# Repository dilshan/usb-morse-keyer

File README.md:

# USB Morse Keyer

USB Morse Keyer is microcontroller based keyer with following features:

- USB / straight key / iambic key inputs.
- Support for both *standalone* and *USB* operating modes.
- 64-character USB typeahead buffer and 6-character Morse key typeahead buffer.
- Support 5, 10, 15 WPM.
- 6-page message memory.
- 1W Audio output.
- Audio and PTT output interfaces.
- 32 character display

To reduce the dimension of the PCB this unit is designed with combining both through-hole and surface mount components. To facilitate future upgrades and modifications, the *PIC16F886* MCU sticks with the standard 28-pin DIP package.

The USB interface of this unit is designed to work with most of the operating systems. It emulates a virtual serial terminal to transfer keystrokes to the keyer. In most of the operating systems, this interface works without installing any additional device drivers. To submit keystrokes user can use any serial terminal software such as [PuTTY](https://www.putty.org), *Hyper Terminal*, [Minicom](https://salsa.debian.org/minicom-team/minicom), etc. 

This keyer is designed to work with 7V to 16V DC input voltage. The most recommended working voltage is 9V.

[All the details related to this project are available at project documentation.](https://github.com/dilshan/usb-morse-keyer/wiki)

## Licenses

This is a [certified](https://certification.oshwa.org/lk000004.html) open hardware project and all it's design files, firmware source codes, [documentation](https://github.com/dilshan/usb-morse-keyer/wiki), and other resource files are available at the project source repository. All the content of this project are distributed under the terms of the following license:

- Hardware License: [CC BY 4.0](https://creativecommons.org/licenses/by/4.0/)
- Software License: [MIT](https://github.com/dilshan/usb-morse-keyer/blob/master/LICENSE)
- Documentation License: [CC BY 4.0](https://creativecommons.org/licenses/by/4.0/)

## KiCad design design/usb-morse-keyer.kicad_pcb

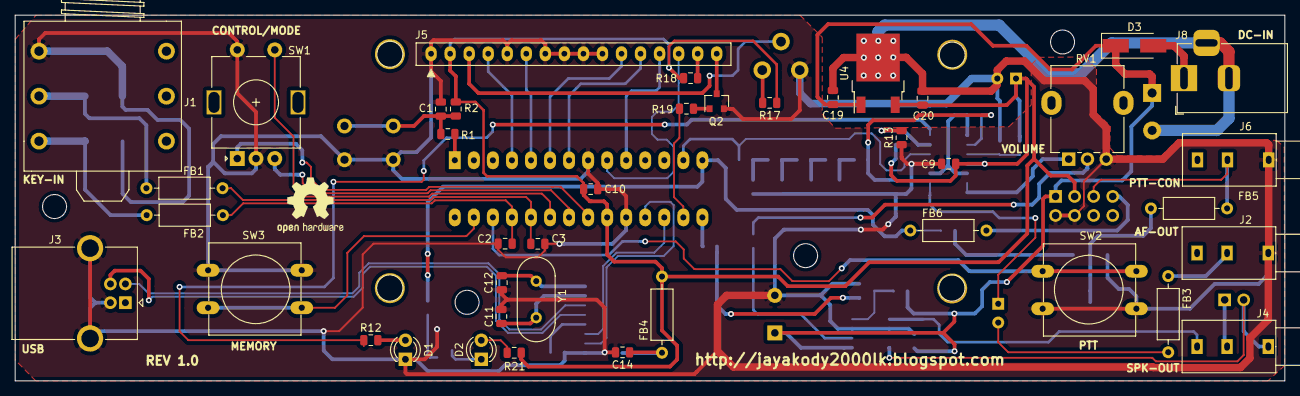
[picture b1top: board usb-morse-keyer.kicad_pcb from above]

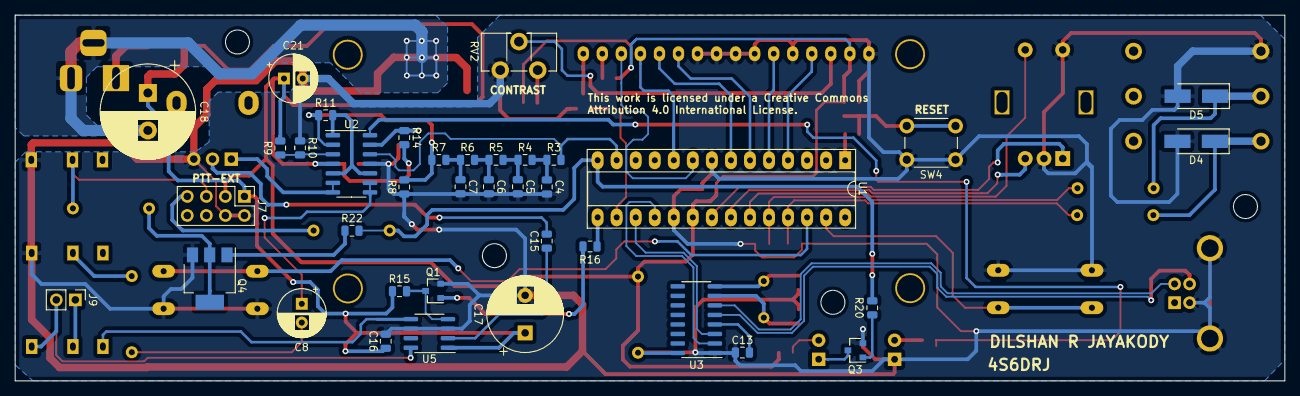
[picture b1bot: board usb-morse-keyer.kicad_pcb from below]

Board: 2 copper layers, 169.3 x 48.8 mm, 83 parts (38 on the bottom side), 66 nets.

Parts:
 : MountingHole_3.2mm_M3_ISO14580
 #2,  #3,  #4: MountingHole_3.2mm_M3_ISO14580
C1, C9, C10, C13, C14, C16, C20: 0.1MFD; C_0805_2012Metric
C2, C3: 0.068MFD; C_0805_2012Metric
C4, C5, C6, C7: 0.15MFD; C_0805_2012Metric
C8: 1MFD; CP_Radial_D6.3mm_P2.50mm
C11, C12: 22pF; C_0805_2012Metric
C15: 0.47MFD; C_0805_2012Metric
C17: 220MFD; CP_Radial_D10.0mm_P5.00mm
C18: 470MFD; CP_Radial_D12.5mm_P5.00mm
C19: 0.22MFD; C_0805_2012Metric
C21: 10MFD; CP_Radial_D6.3mm_P2.50mm
D1: 3mm LED (GREEN); LED_D3.0mm
D2: 3mm LED (RED); LED_D3.0mm
D3: SS14; D_SMA_Handsoldering
D4, D5: SMAJ6.0CA; D_SMA_Handsoldering
FB1, FB2, FB3, FB4, FB5, FB6: EXCELSV35S; L_Axial_L6.6mm_D2.7mm_P10.16mm_Horizontal_Vishay_IM-2
J1: PSG02952; 6.35mm-Jack-Socket-Stereo
J2, J4, J6: FC68102; 3.5mm-Jack-Socket-Mono
J3: MC32596; USB_B_OST_USB-B1HSxx_Horizontal
J5: LCD-1602; 1602-LCD-Module
J7: PTT-EXT; PinHeader_2x04_P2.54mm_Vertical
J8: DC-IN; BarrelJack_Horizontal
J9: SPK-8R; PinHeader_1x02_P2.54mm_Vertical
Q1, Q2, Q3: J3Y; SOT-23
Q4: BCP56; SOT-223
R1, R7, R12, R17: 1K; R_0805_2012Metric
R2, R15, R16, R19, R20, R22: 10K; R_0805_2012Metric
R3, R4, R5, R6: 1.2K; R_0805_2012Metric
R8: 22K; R_0805_2012Metric
R9, R10, R13, R14: 100K; R_0805_2012Metric
R11: 2.2K; R_0805_2012Metric
R18: 560R; R_0805_2012Metric
R21: 4.7K; R_0805_2012Metric
RV1: B20K; Potentiometer_Alpha_RD901F-40-00D_Single_Vertical
RV2: 20K; Potentiometer_ACP_CA9-H3,8_Horizontal
SW1: EC11; RotaryEncoder_Alps_EC11E-Switch_Vertical_H20mm
SW2: PTT; SW_PUSH-12mm
SW3: MEM-MAN; SW_PUSH-12mm
SW4: RESET; SW_PUSH_6mm
U1: PIC16F886IP; DIP-28_W7.62mm_Socket_LongPads
U2: LM324; SOIC-14_3.9x8.7mm_P1.27mm
U3: CH340G; SOIC-16_3.9x9.9mm_P1.27mm
U4: L78M05; TO-252-2
U5: TDA7052A; SOIC-8_3.9x4.9mm_P1.27mm
Y1: 12.00MHz; Crystal_HC49-U_Vertical

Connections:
+5V: C9.1, C10.1, C20.1, C21.1, FB4.2, J5.2, J7.3, R2.2, R9.2, R14.2, R17.2, R18.2, R21.2, U1.20, U2.4, U4.3
+12V: C16.1, C17.1, C18.1, C19.1, D3.1, J7.1, R15.1, U4.1, U5.1
AF-PWM-OUT: R3.2, U1.13, U2.12
AF-PWR-IN: C15.2, RV1.2
AF-SOUT: R11.2, U2.1, U2.5, U2.10
AUDIO-MUTE: R16.2, U1.15
BTN-MEM-MAN: SW3.2, U1.27
BTN-PTT-OVR: SW2.2, U1.26
GND: C1.2, C2.2, C3.2, C4.2, C5.2, C6.2, C7.2, C9.2, C10.2, C11.2, C12.2, C13.1, C14.2, C16.2, C17.2, C18.2, C19.2, C20.2, C21.2, D1.1, D4.2, D5.2, J1.G, J2.S, J3.4, J3.5, J5.1, J5.5, J5.7, J5.8, J5.9, J5.10, J6.S, J7.2, J7.4, J8.2, J8.3, Q1.2, Q2.2, Q3.2, Q4.3, R8.1, R10.1, R13.1, RV1.3, RV2.1, SW1.C, SW1.S2, SW2.1, SW3.1, SW4.1, U1.8, U1.19, U2.11, U3.1, U4.2, U5.3, U5.6
IN-KEY1: C3.1, FB1.1, U1.24
IN-KEY2: C2.1, FB2.1, U1.25
LCD-BK: R19.2, U1.16
LCD-D4: J5.11, U1.6
LCD-D5: J5.12, U1.7
LCD-D6: J5.13, U1.10
LCD-D7: J5.14, U1.9
LCD-EN: J5.6, U1.5
LCD-RS: J5.4, U1.4
unnamed: C4.1, R3.1, R4.2
unnamed: C5.1, R4.1, R5.2
unnamed: C6.1, R5.1, R6.2
unnamed: C7.1, R6.1, R7.2
unnamed: C8.1, U2.8, U2.9
unnamed: C8.2, FB3.2
unnamed: C11.1, U3.7, Y1.1
unnamed: C12.1, U3.8, Y1.2
unnamed: C13.2, U3.4
unnamed: C14.1, FB4.1, U3.16
unnamed: C15.1, U5.2
unnamed: D1.2, R12.2
unnamed: D2.1, Q3.3
unnamed: D2.2, R21.1
unnamed: D3.2, J8.1
unnamed: D4.1, FB2.2, J1.T
unnamed: D5.1, FB1.2, J1.S
unnamed: FB3.1, J2.T
unnamed: FB5.2, Q4.2, Q4.4
unnamed: FB6.1, J7.7
unnamed: J3.2, U3.6
unnamed: J3.3, U3.5
unnamed: J4.S, J9.2, U5.8
unnamed: J4.T, J9.1
unnamed: J4.TN, U5.5
unnamed: J5.3, RV2.2
unnamed: J5.15, R18.1
unnamed: J5.16, Q2.3
unnamed: Q1.1, R16.1
unnamed: Q1.3, R15.2, U5.4
unnamed: Q2.1, R19.1
unnamed: Q3.1, R20.1
unnamed: Q4.1, R22.1
unnamed: R1.1, U1.1
unnamed: R9.1, R10.2, U2.3
unnamed: R7.1, R8.2, R11.1, U2.2
unnamed: R12.1, U2.14
unnamed: R13.2, R14.1, U2.13
unnamed: R17.1, RV2.3
unnamed: RV1.1, U2.6, U2.7
PTT-OC-OUT: FB5.1, J6.T, J7.5
PTT-OUT: FB6.2, R20.2, R22.2, U1.14
RESET: C1.1, R1.2, R2.1, SW4.2
ROT-RA: SW1.A, U1.21
ROT-RB: SW1.B, U1.22
ROT-SD: SW1.S1, U1.23
RXD: U1.17, U3.3
TXD: U1.18, U3.2

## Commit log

2019-08-22 Initial version of project files.
2019-08-22 Update project readme file with initial draft.
2019-08-22 Update readme file with sections.
2019-08-24 Fix specification error in readme file.
2019-08-24 Add link to project documentation.
2019-08-24 Add badges to the readme file.
2019-08-26 Add OSHWA certification information.

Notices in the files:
design/usb-morse-keyer.kicad_pcb:
This work is licensed under a Creative Commons
Attribution 4.0 International License.
